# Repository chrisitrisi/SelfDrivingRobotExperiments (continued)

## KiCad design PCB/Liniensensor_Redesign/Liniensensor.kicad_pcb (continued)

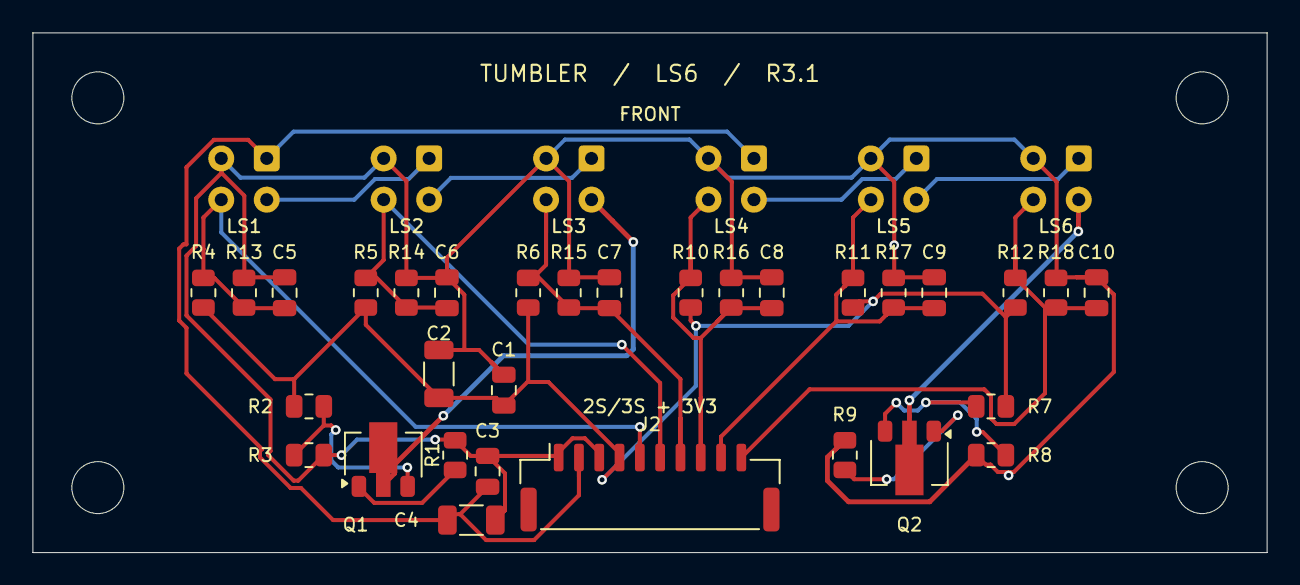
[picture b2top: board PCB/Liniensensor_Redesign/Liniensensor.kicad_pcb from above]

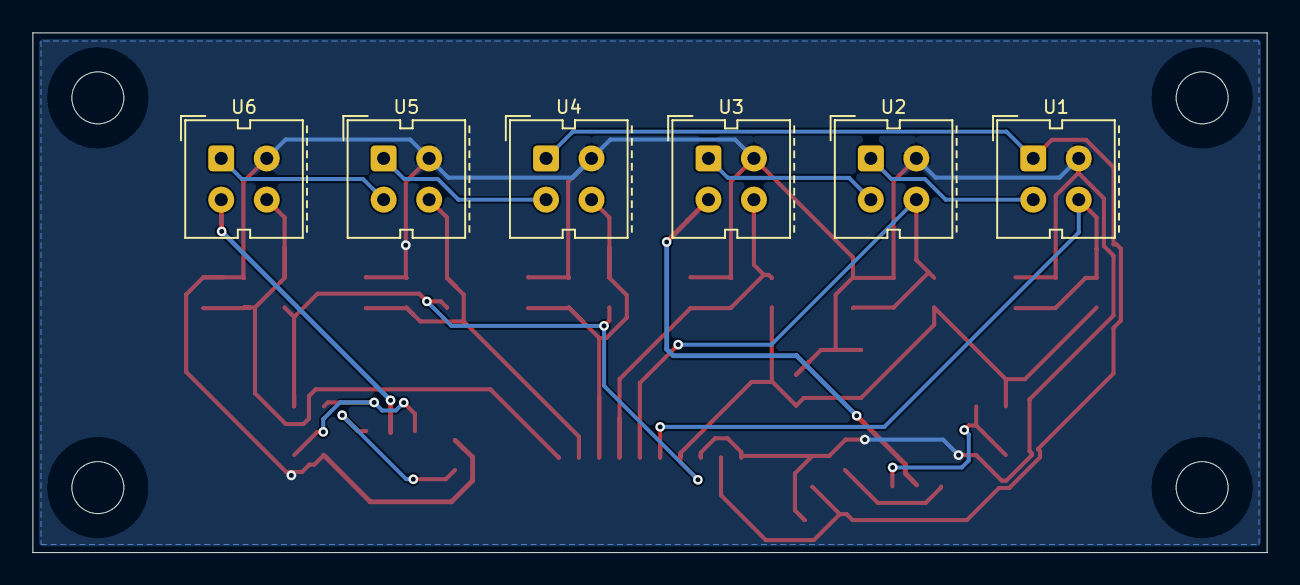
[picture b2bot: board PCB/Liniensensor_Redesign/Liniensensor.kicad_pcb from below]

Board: 2 copper layers, 76.0 x 32.0 mm, 41 parts (6 on the bottom side), 19 nets.

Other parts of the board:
H1, H2, H3, H4: MountingHole_3.2mm_M3

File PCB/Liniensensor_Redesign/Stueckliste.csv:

Reference;Value;Footprint;Manufacturer;MPN;Rating;Datasheet
C1;100n / 50V;Capacitor_SMD:C_0805_2012Metric;KEMET / Yageo;C0805C104K5RACTU;"10%; X7R; 50 V";https://search.kemet.com/download/specsheet/C0805C104K5RAC7800
C2;10u / 25V;Capacitor_SMD:C_1206_3216Metric;TDK;C3216X7R1E106K160AB;"10%; X7R; 25 V";https://product.tdk.com/en/search/capacitor/ceramic/mlcc/inf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
C3;100n / 50V;Capacitor_SMD:C_0805_2012Metric;KEMET / Yageo;C0805C104K5RACTU;"10%; X7R; 50 V";https://search.kemet.com/download/specsheet/C0805C104K5RAC7800
C4;10u / 25V;Capacitor_SMD:C_1206_3216Metric;TDK;C3216X7R1E106K160AB;"10%; X7R; 25 V";https://product.tdk.com/en/search/capacitor/ceramic/mlcc/inf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
C5;10n / 50V;Capacitor_SMD:C_0805_2012Metric;KEMET / Yageo;C0805C103K5RACTU;"10%; X7R; 50 V";https://search.kemet.com/download/specsheet/C0805C103K5RAC7800
C6;10n / 50V;Capacitor_SMD:C_0805_2012Metric;KEMET / Yageo;C0805C103K5RACTU;"10%; X7R; 50 V";https://search.kemet.com/download/specsheet/C0805C103K5RAC7800
C7;10n / 50V;Capacitor_SMD:C_0805_2012Metric;KEMET / Yageo;C0805C103K5RACTU;"10%; X7R; 50 V";https://search.kemet.com/download/specsheet/C0805C103K5RAC7800
C8;10n / 50V;Capacitor_SMD:C_0805_2012Metric;KEMET / Yageo;C0805C103K5RACTU;"10%; X7R; 50 V";https://search.kemet.com/download/specsheet/C0805C103K5RAC7800
C9;10n / 50V;Capacitor_SMD:C_0805_2012Metric;KEMET / Yageo;C0805C103K5RACTU;"10%; X7R; 50 V";https://search.kemet.com/download/specsheet/C0805C103K5RAC7800
C10;10n / 50V;Capacitor_SMD:C_0805_2012Metric;KEMET / Yageo;C0805C103K5RACTU;"10%; X7R; 50 V";https://search.kemet.com/download/specsheet/C0805C103K5RAC7800
J2;JST GH 10-pol.;Connector_JST:JST_GH_SM10B-GHS-TB_1x10-1MP_P1.25mm_Horizontal;JST;SM10B-GHS-TB(LF)(SN);"1.25 mm; 1 A with AWG26; 50 V";https://www.jst-mfg.com/product/pdf/eng/eGH.pdf
Q1;BCX56-16;Package_TO_SOT_SMD:SOT-89-3;Diodes Inc.;BCX5616QTA;"SOT-89 Pin 1 = E, 2 = C, 3 = B; 80 V; 1 A; Rth(j-a) 250 K/W Minimal-Pad; Tj max 150 C; Alternative Nexperia BCX56-16,115";https://diodes.com/datasheet/download/BCX5616Q.pdf
Q2;BCX56-16;Package_TO_SOT_SMD:SOT-89-3;Diodes Inc.;BCX5616QTA;"SOT-89 Pin 1 = E, 2 = C, 3 = B; 80 V; 1 A; Rth(j-a) 250 K/W Minimal-Pad; Tj max 150 C; Alternative Nexperia BCX56-16,115";https://diodes.com/datasheet/download/BCX5616Q.pdf
R1;47;Resistor_SMD:R_0805_2012Metric;Vishay;CRCW080547R0FKEA;"1%; 0.125 W (standard mode, P70)";https://www.vishay.com/docs/20035/dcrcwe3.pdf
R2;470;Resistor_SMD:R_0805_2012Metric;Vishay;CRCW0805470RFKEA;"1%; 0.125 W (standard mode, P70)";https://www.vishay.com/docs/20035/dcrcwe3.pdf
R3;470;Resistor_SMD:R_0805_2012Metric;Vishay;CRCW0805470RFKEA;"1%; 0.125 W (standard mode, P70)";https://www.vishay.com/docs/20035/dcrcwe3.pdf
R4;10k;Resistor_SMD:R_0805_2012Metric;Vishay;CRCW080510K0FKEA;"1%; 0.125 W (standard mode, P70)";https://www.vishay.com/docs/20035/dcrcwe3.pdf
R5;10k;Resistor_SMD:R_0805_2012Metric;Vishay;CRCW080510K0FKEA;"1%; 0.125 W (standard mode, P70)";https://www.vishay.com/docs/20035/dcrcwe3.pdf
R6;10k;Resistor_SMD:R_0805_2012Metric;Vishay;CRCW080510K0FKEA;"1%; 0.125 W (standard mode, P70)";https://www.vishay.com/docs/20035/dcrcwe3.pdf
R7;470;Resistor_SMD:R_0805_2012Metric;Vishay;CRCW0805470RFKEA;"1%; 0.125 W (standard mode, P70)";https://www.vishay.com/docs/20035/dcrcwe3.pdf
R8;470;Resistor_SMD:R_0805_2012Metric;Vishay;CRCW0805470RFKEA;"1%; 0.125 W (standard mode, P70)";https://www.vishay.com/docs/20035/dcrcwe3.pdf
R9;47;Resistor_SMD:R_0805_2012Metric;Vishay;CRCW080547R0FKEA;"1%; 0.125 W (standard mode, P70)";https://www.vishay.com/docs/20035/dcrcwe3.pdf
R10;10k;Resistor_SMD:R_0805_2012Metric;Vishay;CRCW080510K0FKEA;"1%; 0.125 W (standard mode, P70)";https://www.vishay.com/docs/20035/dcrcwe3.pdf
R11;10k;Resistor_SMD:R_0805_2012Metric;Vishay;CRCW080510K0FKEA;"1%; 0.125 W (standard mode, P70)";https://www.vishay.com/docs/20035/dcrcwe3.pdf
R12;10k;Resistor_SMD:R_0805_2012Metric;Vishay;CRCW080510K0FKEA;"1%; 0.125 W (standard mode, P70)";https://www.vishay.com/docs/20035/dcrcwe3.pdf
R13;47k;Resistor_SMD:R_0805_2012Metric;Vishay;CRCW080547K0FKEA;"1%; 0.125 W (standard mode, P70)";https://www.vishay.com/docs/20035/dcrcwe3.pdf
R14;47k;Resistor_SMD:R_0805_2012Metric;Vishay;CRCW080547K0FKEA;"1%; 0.125 W (standard mode, P70)";https://www.vishay.com/docs/20035/dcrcwe3.pdf
R15;47k;Resistor_SMD:R_0805_2012Metric;Vishay;CRCW080547K0FKEA;"1%; 0.125 W (standard mode, P70)";https://www.vishay.com/docs/20035/dcrcwe3.pdf
R16;47k;Resistor_SMD:R_0805_2012Metric;Vishay;CRCW080547K0FKEA;"1%; 0.125 W (standard mode, P70)";https://www.vishay.com/docs/20035/dcrcwe3.pdf
R17;47k;Resistor_SMD:R_0805_2012Metric;Vishay;CRCW080547K0FKEA;"1%; 0.125 W (standard mode, P70)";https://www.vishay.com/docs/20035/dcrcwe3.pdf
R18;47k;Resistor_SMD:R_0805_2012Metric;Vishay;CRCW080547K0FKEA;"1%; 0.125 W (standard mode, P70)";https://www.vishay.com/docs/20035/dcrcwe3.pdf
U1;CNY70;OptoDevice:Vishay_CNY70;Vishay;CNY70;"IF design ~20 mA; absolute maximum 50 mA";https://www.vishay.com/docs/83751/cny70.pdf
U2;CNY70;OptoDevice:Vishay_CNY70;Vishay;CNY70;"IF design ~20 mA; absolute maximum 50 mA";https://www.vishay.com/docs/83751/cny70.pdf
U3;CNY70;OptoDevice:Vishay_CNY70;Vishay;CNY70;"IF design ~20 mA; absolute maximum 50 mA";https://www.vishay.com/docs/83751/cny70.pdf
U4;CNY70;OptoDevice:Vishay_CNY70;Vishay;CNY70;"IF design ~20 mA; absolute maximum 50 mA";https://www.vishay.com/docs/83751/cny70.pdf
U5;CNY70;OptoDevice:Vishay_CNY70;Vishay;CNY70;"IF design ~20 mA; absolute maximum 50 mA";https://www.vishay.com/docs/83751/cny70.pdf
U6;CNY70;OptoDevice:Vishay_CNY70;Vishay;CNY70;"IF design ~20 mA; absolute maximum 50 mA";https://www.vishay.com/docs/83751/cny70.pdf

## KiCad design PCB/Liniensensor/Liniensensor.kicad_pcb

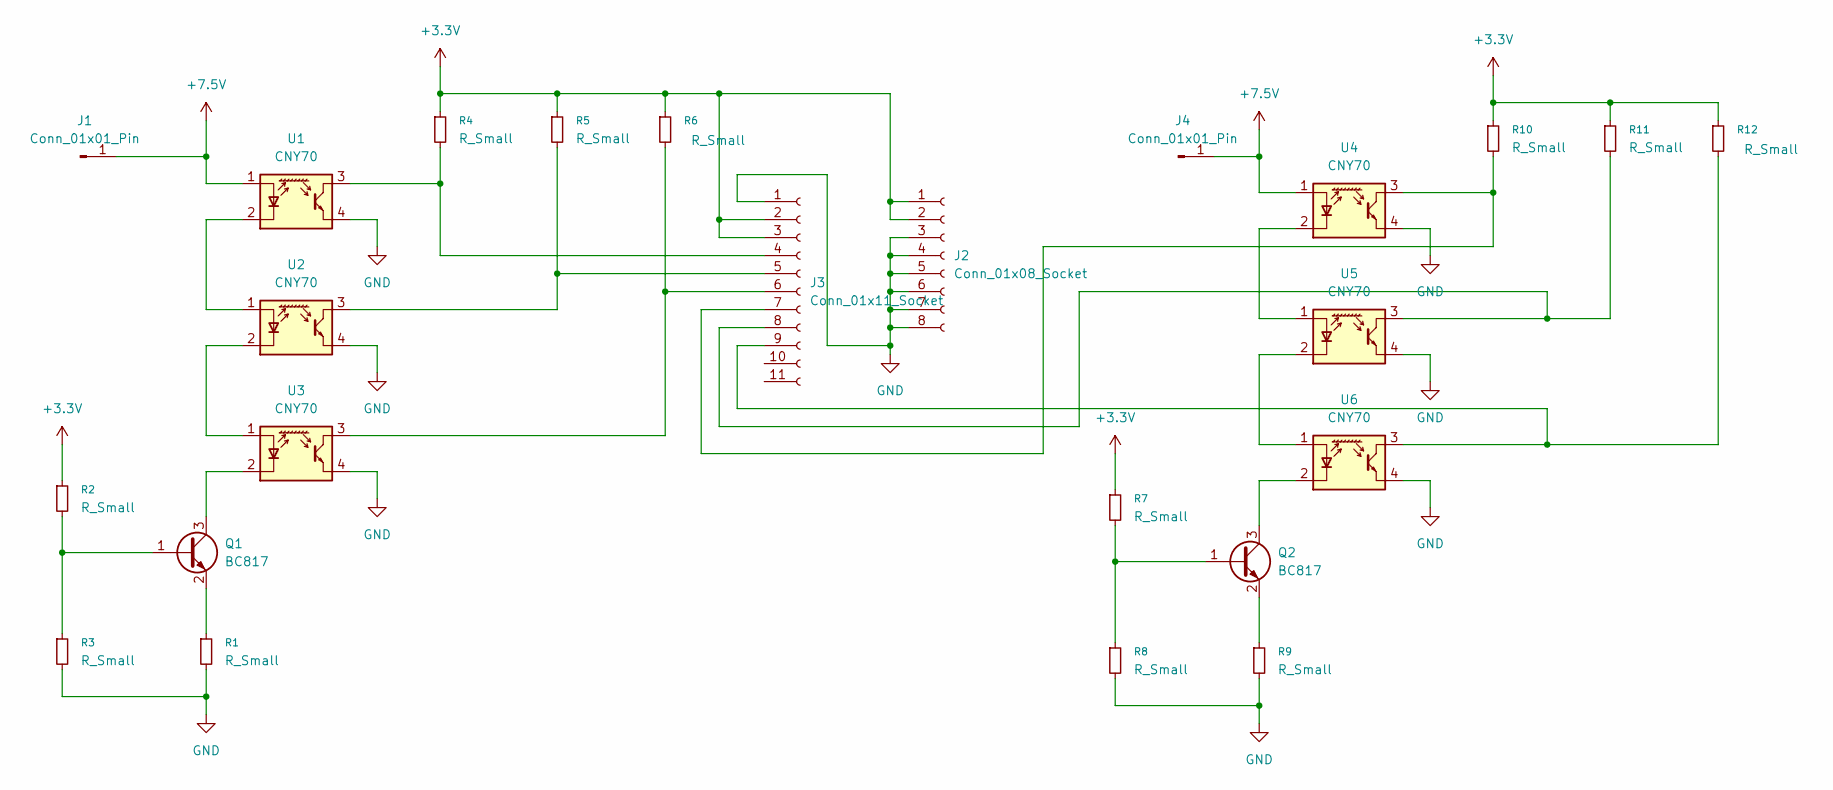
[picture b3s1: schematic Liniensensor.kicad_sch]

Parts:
J1, J4: Conn_01x01_Pin; SolderWire-0.127sqmm_1x01_D0.48mm_OD1mm
J2: Conn_01x08_Socket; PinSocket_1x08_P2.54mm_Vertical
J3: Conn_01x11_Socket; PinSocket_1x11_P2.54mm_Vertical
Q1, Q2: BC817; SOT-23
R1, R2, R3, R7, R8, R9: R_Small; R_0805_2012Metric_Pad1.20x1.40mm_HandSolder
R4, R5, R6, R10, R11, R12: R_Small; R_Axial_DIN0207_L6.3mm_D2.5mm_P7.62mm_Horizontal
U1, U2, U3, U4, U5, U6: CNY70; Vishay_CNY70

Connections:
+3.3V: J2.1, J2.2, J3.2, J3.3, R2.1, R4.1, R5.1, R6.1, R7.1, R10.1, R11.1, R12.1
+7.5V: J1.1, J4.1, U1.1 (A), U4.1 (A)
GND: J2.3, J2.4, J2.5, J2.6, J2.7, J2.8, J3.1, R1.2, R3.2, R8.2, R9.2, U1.4 (E), U2.4 (E), U3.4 (E), U4.4 (E), U5.4 (E), U6.4 (E)
unnamed: J3.4, R4.2, U1.3 (C)
unnamed: J3.5, R5.2, U2.3 (C)
unnamed: J3.6, R6.2, U3.3 (C)
unnamed: J3.7, R10.2, U4.3 (C)
unnamed: J3.8, R11.2, U5.3 (C)
unnamed: J3.9, R12.2, U6.3 (C)
unnamed: Q1.1 (B), R2.2, R3.1
unnamed: Q1.3 (C), U3.2 (K)
unnamed: Q1.2 (E), R1.1
unnamed: Q2.1 (B), R7.2, R8.1
unnamed: Q2.3 (C), U6.2 (K)
unnamed: Q2.2 (E), R9.1
unnamed: U1.2 (K), U2.1 (A)
unnamed: U2.2 (K), U3.1 (A)
unnamed: U4.2 (K), U5.1 (A)
unnamed: U5.2 (K), U6.1 (A)

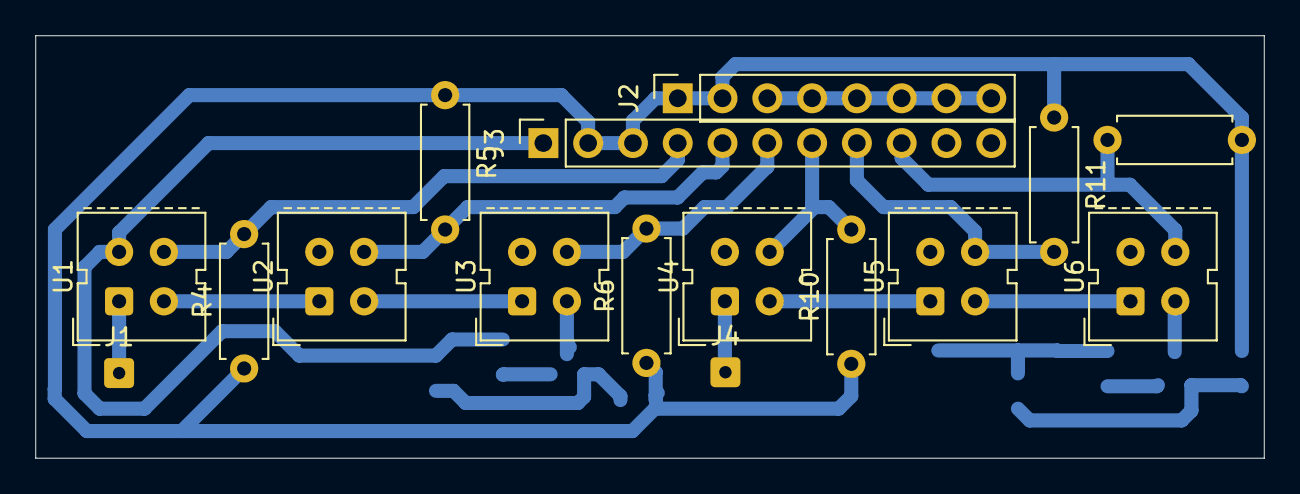
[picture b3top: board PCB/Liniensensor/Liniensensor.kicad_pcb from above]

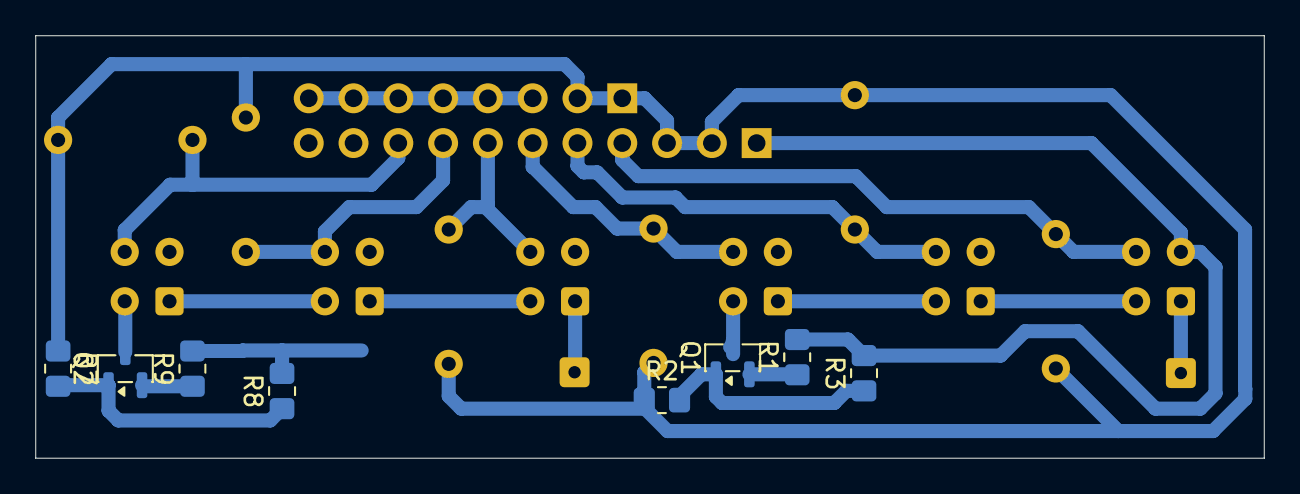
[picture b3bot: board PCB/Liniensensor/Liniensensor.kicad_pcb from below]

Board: 2 copper layers, 69.7 x 24.0 mm, 24 parts (8 on the bottom side), 19 nets.

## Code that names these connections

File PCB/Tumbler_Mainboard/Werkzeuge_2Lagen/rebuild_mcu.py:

import sys,json,uuid,re; sys.path.insert(0,'/tmp/claude-1000/-home-spiderhead87-School-DA/ac92c1f8-fe08-4559-847c-0964da7411fb/scratchpad')
from sx import *
F='mcu.kicad_sch'; text=open(F).read(); sch=parse(text)
A=json.load(open('/tmp/claude-1000/-home-spiderhead87-School-DA/ac92c1f8-fe08-4559-847c-0964da7411fb/scratchpad/2L/assign.json'))
lp=libpins(sch)
u3=[c for c in find(sch,'symbol') if prop(c,'Reference')=='U3'][0]; PP={k:(round(v[0],2),round(v[1],2)) for k,v in pinpos(u3,lp).items()}
allpins=set()
for c in find(sch,'symbol'):
    if prop(c,'Reference') and not prop(c,'Reference').startswith('#'):
        for k,v in pinpos(c,lp).items(): allpins.add((round(v[0],2),round(v[1],2)))
R=lambda p:(round(p[0],2),round(p[1],2))
wires=[]
for c in find(sch,'wire'):
    p=[R((float(q[1]),float(q[2]))) for q in first(c,'pts')[1:]]; wires.append((p,unq(first(c,'uuid')[1])))
labels=[]
for c in sch:
    if isinstance(c,list) and c and c[0] in ('label','hierarchical_label','global_label'):
        a=first(c,'at'); labels.append((c[0],unq(c[1]),R((float(a[1]),float(a[2]))),unq(first(c,'uuid')[1]),c))
entries=[]
for c in find(sch,'bus_entry'):
    a=first(c,'at'); sz=first(c,'size'); p0=R((float(a[1]),float(a[2]))); p1=R((p0[0]+float(sz[1]),p0[1]+float(sz[2])))
    entries.append(((p0,p1),unq(first(c,'uuid')[1])))
juncs=[(R((float(first(c,'at')[1]),float(first(c,'at')[2]))),unq(first(c,'uuid')[1])) for c in find(sch,'junction')]
ncs=[(R((float(first(c,'at')[1]),float(first(c,'at')[2]))),unq(first(c,'uuid')[1])) for c in find(sch,'no_connect')]
def on_seg(p,a,b):
    if a[0]==b[0]==p[0]: return min(a[1],b[1])-1e-6<=p[1]<=max(a[1],b[1])+1e-6
    if a[1]==b[1]==p[1]: return min(a[0],b[0])-1e-6<=p[0]<=max(a[0],b[0])+1e-6
    return p==a or p==b
AFFECT=sorted(set(A.values())|{4,5,6,7,8,9,10,11,12,15,17,18,19,20,21,22,23,24,25,30,31,32,33,34,35,38,39})
kill=set(); sig_labels={}
for pin in AFFECT:
    start=R(PP[str(pin)]); pts={start}; tree=set(); changed=True
    while changed:
        changed=False
        for p,u in wires:
            if u in tree: continue
            if any(on_seg(q,p[0],p[-1]) for q in pts) or any(on_seg(x,*[y for y in [p[0],p[-1]]]) for x in pts if False):
                tree.add(u); pts|={p[0],p[-1]}; changed=True
        for (p0,p1),u in entries:
            if u in tree: continue
            if p0 in pts or p1 in pts: tree.add(u); changed=True   # Bus-Eintrag gehoert dazu, aber nicht weiter verfolgen
    others=[q for q in pts if q in allpins and q!=start]
    if others: raise SystemExit(f'Pin {pin}: Drahtbaum fuehrt zu anderem Pin {others}')
    labs=[l for l in labels if any(on_seg(l[2],p[0],p[-1]) for p,u in wires if u in tree) or l[2]==start]
    kill|=tree|{l[3] for l in labs}|{u for q,u in juncs if q in pts}|{u for q,u in ncs if q==start}
    sig_labels[pin]=labs
# Signal -> Labels (vom alten Pin)
OLDPIN={'LS1':4,'LS2':5,'LS3':6,'LS4':7,'BTN':8,'ECHO':9,'SPARE1':10,'SPARE2':11,'RGB':12,'BAT_ADC':15,'LS5':17,'LS6':18,'TRIG':19,'INT1':20,'SDA':21,'SCL':22,'ENCA_A':23,'PWMA':24,'DIR_A':25,'MUX_RSTn':30,'ENCB_A':31,'MOTOR_STBY':32,'USB_PRESENTn':33,'DIR_B':34,'PWMB':35,'ENCA_B':38,'ENCB_B':39}
for s,p in OLDPIN.items():
    names={l[1] for l in sig_labels[p]}
    print(s,'alt Pin',p,'Labels',[(l[0],l[1]) for l in sig_labels[p]])
# Objekte entfernen (Top-Level-Bloecke mit diesen UUIDs)
def remove_blocks(t,uuids):
    out=[];i=0;n=0
    lines=t.split('\n'); res=[]; skip=False; buf=[]
    # Blockweise auf Top-Level (eine Tab-Einrueckung)
    blocks=re.split(r'(?m)^(?=\t\()',t)
    keep=[]
    for b in blocks:
        m=re.search(r'\(uuid "([^"]+)"\)',b)
        head=b.lstrip('\t').split('\n')[0]
        if m and m.group(1) in uuids and re.match(r'\((wire|label|hierarchical_label|global_label|bus_entry|junction|no_connect)\b',head):
            n+=1; continue
        keep.append(b)
    return ''.join(keep),n
text,n=remove_blocks(text,kill); print('entfernt',n,'Objekte')
# Neu aufbauen
new=[]
def wire(a,b): return f'\t(wire\n\t\t(pts\n\t\t\t(xy {a[0]} {a[1]}) (xy {b[0]} {b[1]})\n\t\t)\n\t\t(stroke\n\t\t\t(width 0)\n\t\t\t(type default)\n\t\t)\n\t\t(uuid "{uuid.uuid4()}")\n\t)\n'
def relabel(lab,name,x,y,ang):
    kind=lab[0]; blk=lab[4]
    j=('left' if ang==0 else 'right')+(' bottom' if kind=='label' else '')
    shape=first(blk,'shape')
    s=f'\t({kind} "{name}"\n'
    if shape: s+=f'\t\t(shape {shape[1]})\n'
    s+=f'\t\t(at {x} {y} {ang})\n\t\t(effects\n\t\t\t(font\n\t\t\t\t(size 1.27 1.27)\n\t\t\t)\n\t\t\t(justify {j})\n\t\t)\n\t\t(uuid "{uuid.uuid4()}")\n'
    if kind=='global_label': s+=f'\t\t(property "Intersheetrefs" "${{INTERSHEET_REFS}}"\n\t\t\t(at {x} {y} {ang})\n\t\t\t(hide yes)\n\t\t\t(effects\n\t\t\t\t(font\n\t\t\t\t\t(size 1.27 1.27)\n\t\t\t\t)\n\t\t\t)\n\t\t)\n'
    return s+'\t)\n'
used=set()
for sig,newpin in A.items():
    px,py=PP[str(newpin)]; left=px<106; d=-1 if left else 1
    end=(round(px+d*7.62,2),py); mid=(round(px+d*3.81,2),py)
    new.append(wire((px,py),end)); used.add(newpin)
    labs=sig_labels[OLDPIN[sig]]
    # nach Typ sortieren: hierarchisch/global ans Ende, lokale in die Mitte
    labs=sorted(labs,key=lambda l:0 if l[0]!='label' else 1)
    seen=set()
    for k,l in enumerate(labs):
        name=sig if sig.startswith('SPARE') else l[1]
        if (l[0],name) in seen: continue
        seen.add((l[0],name))
        pos=end if k==0 else mid
        new.append(relabel(l,name,pos[0],pos[1],180 if left else 0))
for pin in AFFECT:
    if pin not in used:
        px,py=PP[str(pin)]; new.append(f'\t(no_connect\n\t\t(at {px} {py})\n\t\t(uuid "{uuid.uuid4()}")\n\t)\n'); print('NC an Pin',pin)
# J3-seitige IO17/IO18 umbenennen
text=text.replace('(label "IO17"','(label "SPARE1"').replace('(label "IO18"','(label "SPARE2"')
idx=text.rstrip().rindex(')')-1
text=text[:idx+1]+''.join(new)+text[idx+1:]
open(F,'w').write(text); print('fertig')
